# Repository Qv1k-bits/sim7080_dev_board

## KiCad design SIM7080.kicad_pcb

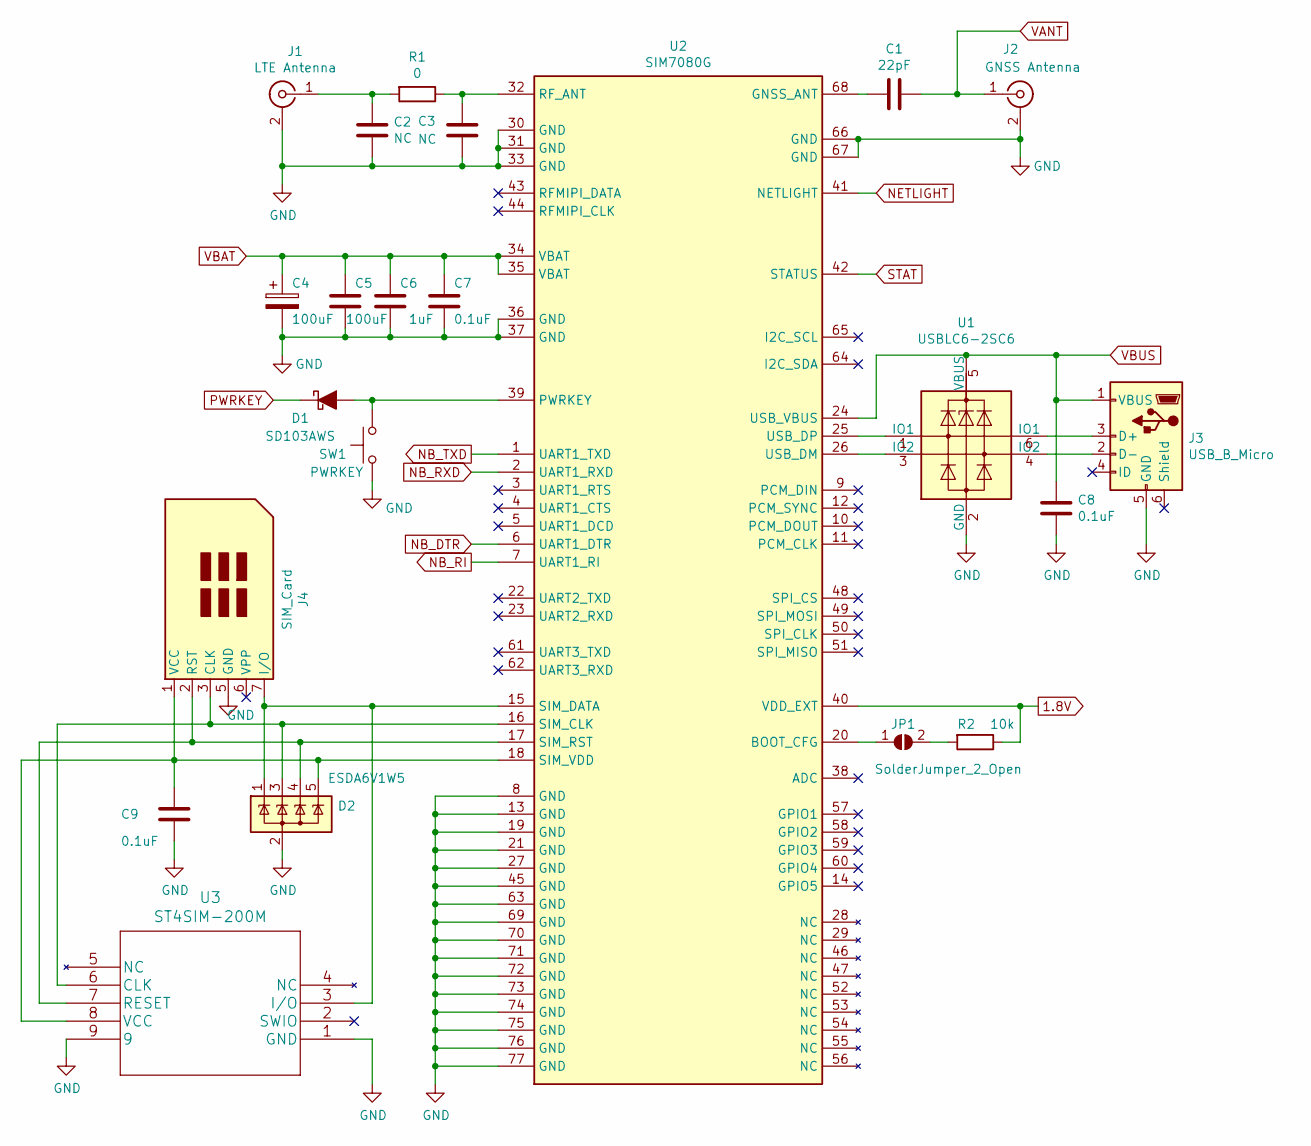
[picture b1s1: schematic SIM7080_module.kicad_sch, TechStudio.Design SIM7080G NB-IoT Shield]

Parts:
C1: 22pF; C_0603_1608Metric_Pad1.05x0.95mm_HandSolder
C2, C3: NC; C_0603_1608Metric_Pad1.05x0.95mm_HandSolder
C4: 100uF; CP_EIA-3528-12_Kemet-T_Pad1.50x2.35mm_HandSolder
C5: 100uF; C_1206_3216Metric_Pad1.42x1.75mm_HandSolder
C6: 1uF; C_0603_1608Metric_Pad1.05x0.95mm_HandSolder
C7, C8, C9: 0.1uF; C_0603_1608Metric_Pad1.05x0.95mm_HandSolder
D1: SD103AWS; D_SOD-323_HandSoldering
D2: ESDA6V1W5; SOT-353_SC-70-5_Handsoldering
J1: LTE Antenna; U.FL_Hirose_U.FL-R-SMT-1_Vertical
J2: GNSS Antenna; U.FL_Hirose_U.FL-R-SMT-1_Vertical
J3: USB_B_Micro; U254-051T-4BH83
J4: SIM_Card; HOAUC-HYC240-SIM-06-150_C645501
JP1: SolderJumper_2_Open; SolderJumper-2_P1.3mm_Open_Pad1.0x1.5mm
R1: 0; R_0603_1608Metric_Pad1.05x0.95mm_HandSolder
R2: 10k; R_0603_1608Metric_Pad1.05x0.95mm_HandSolder
SW1: PWRKEY; SW_TS-1101-X-X
U1: USBLC6-2SC6; SOT-23-6_Handsoldering
U2: SIM7080G
U3: ST4SIM-200M

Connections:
1.8V: R2.1, U2.40 (VDD_EXT); also elsewhere on the board
GND: C2.2, C3.2, C4.2, C5.2, C6.2, C7.2, C8.2, C9.2, D2.2 (A), J1.2 (Ext), J2.2 (Ext), J3.5 (GND), J4.5 (GND), SW1.1, U1.2 (GND), U2.8 (GND), U2.13 (GND), U2.19 (GND), U2.21 (GND), U2.27 (GND), U2.30 (GND), U2.31 (GND), U2.33 (GND), U2.36 (GND), U2.37 (GND), U2.45 (GND), U2.63 (GND), U2.66 (GND), U2.67 (GND), U2.69 (GND), U2.70 (GND), U2.71 (GND), U2.72 (GND), U2.73 (GND), U2.74 (GND), U2.75 (GND), U2.76 (GND), U2.77 (GND), U3.1 (GND), U3.9; also elsewhere on the board
NB_DTR: U2.6 (UART1_DTR); also elsewhere on the board
NB_RI: U2.7 (UART1_RI); also elsewhere on the board
NB_RXD: U2.2 (UART1_RXD); also elsewhere on the board
NB_TXD: U2.1 (UART1_TXD); also elsewhere on the board
NETLIGHT: U2.41 (NETLIGHT); also elsewhere on the board
unnamed: C1.1, U2.68 (GNSS_ANT)
unnamed: C2.1, J1.1 (In), R1.2
unnamed: C3.1, R1.1, U2.32 (RF_ANT)
unnamed: C9.1, D2.5 (K), J4.1 (VCC), U2.18 (SIM_VDD), U3.8 (VCC)
unnamed: D1.2 (A), SW1.2, U2.39 (PWRKEY)
unnamed: D2.1 (K), J4.7 (I/O), U2.15 (SIM_DATA), U3.3 (I/O)
unnamed: D2.3 (K), J4.3 (CLK), U2.16 (SIM_CLK), U3.6 (CLK)
unnamed: D2.4 (K), J4.2 (RST), U2.17 (SIM_RST), U3.7 (RESET)
unnamed: J3.2 (D-), U1.4 (IO2)
unnamed: J3.3 (D+), U1.6 (IO1)
unnamed: JP1.1 (A), U2.20 (BOOT_CFG)
unnamed: JP1.2 (B), R2.2
unnamed: U1.1 (IO1), U2.25 (USB_DP)
unnamed: U1.3 (IO2), U2.26 (USB_DM)
PWRKEY: D1.1 (K); also elsewhere on the board
STAT: U2.42 (STATUS); also elsewhere on the board
VANT: C1.2, J2.1 (In); also elsewhere on the board
VBAT: C4.1, C5.1, C6.1, C7.1, U2.34 (VBAT), U2.35 (VBAT); also elsewhere on the board
VBUS: C8.1, J3.1 (VBUS), U1.5 (VBUS), U2.24 (USB_VBUS); also elsewhere on the board

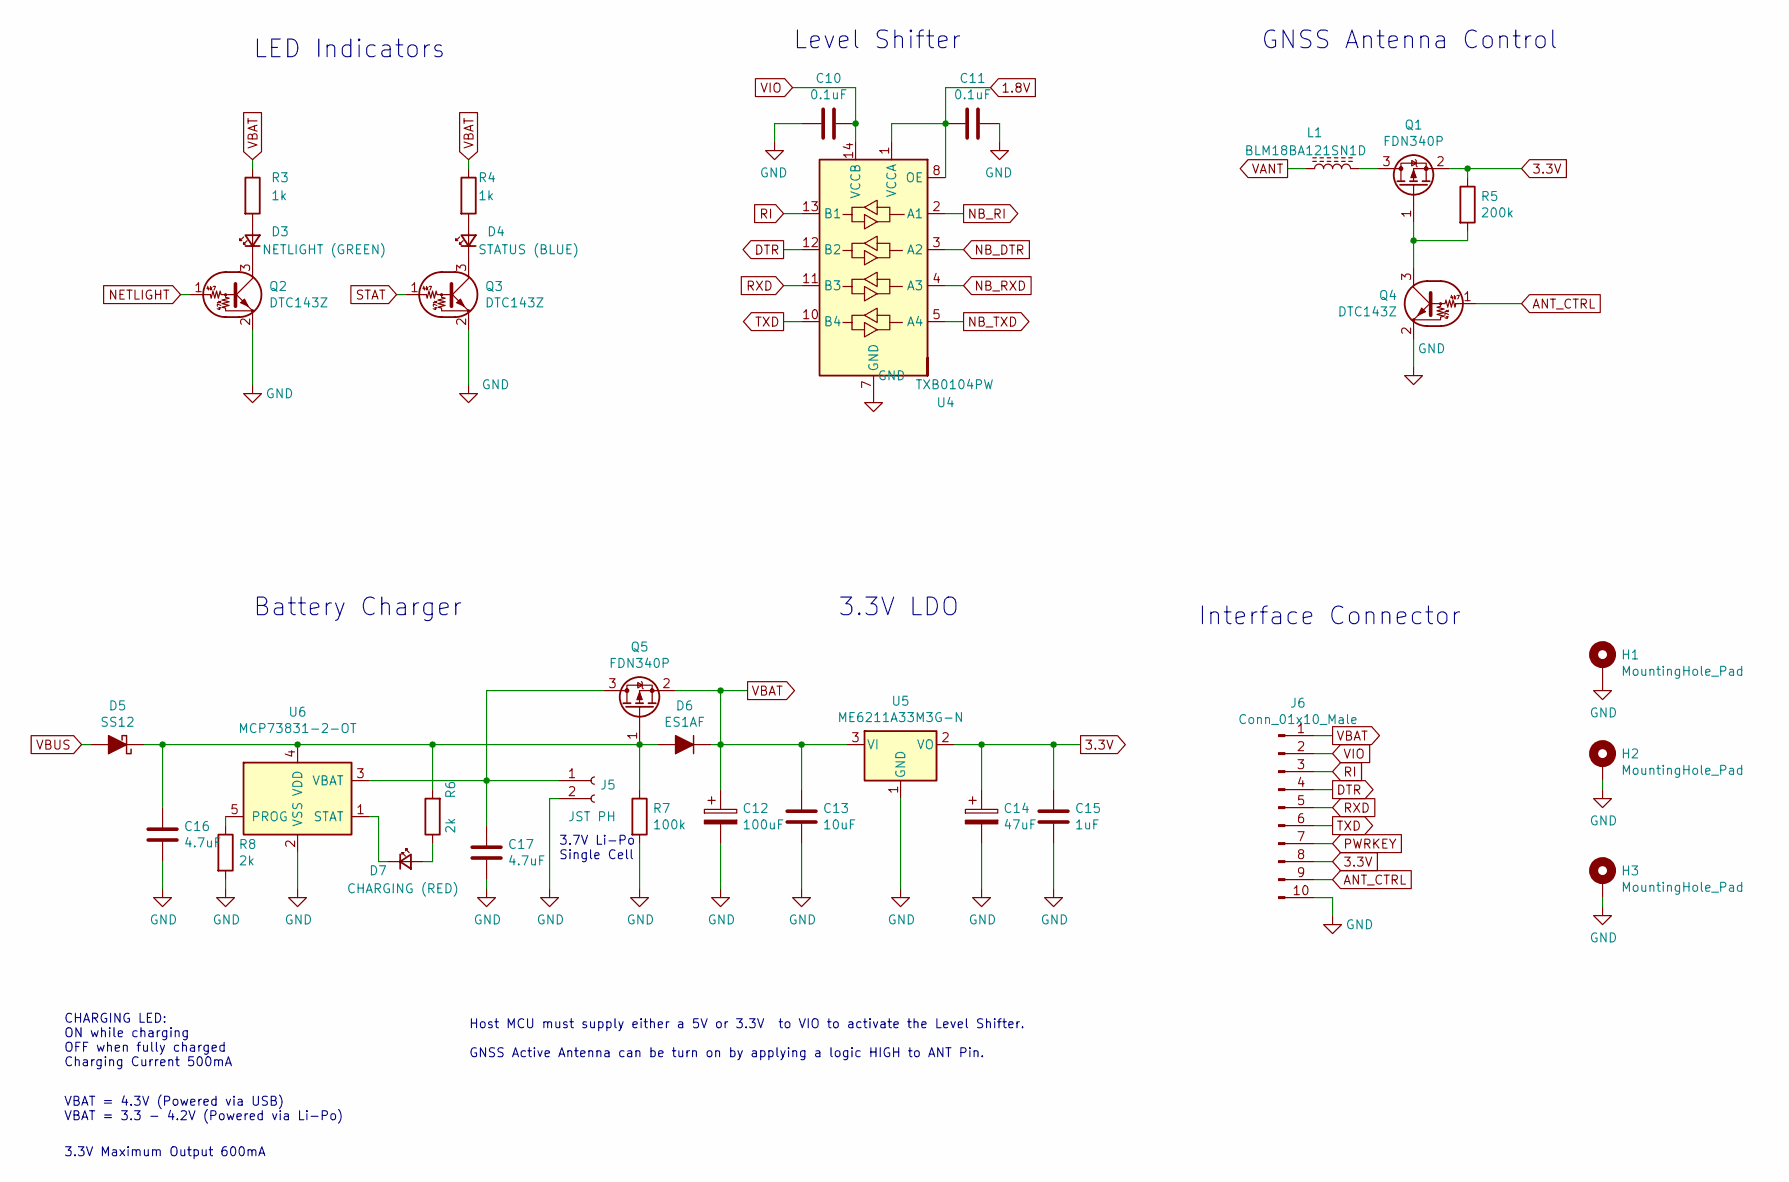
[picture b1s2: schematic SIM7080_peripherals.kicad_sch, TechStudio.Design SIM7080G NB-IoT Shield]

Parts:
C10, C11: 0.1uF; C_0603_1608Metric_Pad1.05x0.95mm_HandSolder
C12: 100uF; CP_EIA-3528-12_Kemet-T_Pad1.50x2.35mm_HandSolder
C13: 10uF; C_0603_1608Metric_Pad1.05x0.95mm_HandSolder
C14: 47uF; CP_EIA-3216-10_Kemet-I_Pad1.58x1.35mm_HandSolder
C15: 1uF; C_0603_1608Metric_Pad1.05x0.95mm_HandSolder
C16, C17: 4.7uF; C_0603_1608Metric_Pad1.05x0.95mm_HandSolder
D3: NETLIGHT (GREEN); LED_0603_1608Metric_Pad1.05x0.95mm_HandSolder
D4: STATUS (BLUE); LED_0603_1608Metric_Pad1.05x0.95mm_HandSolder
D5: SS12; D_SMA
D6: ES1AF; D_SMA
D7: CHARGING (RED); LED_0603_1608Metric_Pad1.05x0.95mm_HandSolder
H1, H2, H3: MountingHole_Pad; MountingHole_2.7mm_M2.5
J5: JST PH; JST_PH_S2B-PH-K_1x02_P2.00mm_Horizontal
J6: Conn_01x10_Male; PinHeader_1x10_P2.54mm_Horizontal
L1: BLM18BA121SN1D; L_0603_1608Metric_Pad1.05x0.95mm_HandSolder
Q1, Q5: FDN340P; SOT-23_Handsoldering
Q2, Q3, Q4: DTC143Z; SOT523
R3, R4: 1k; R_0603_1608Metric_Pad1.05x0.95mm_HandSolder
R5: 200k; R_0603_1608Metric_Pad1.05x0.95mm_HandSolder
R6, R8: 2k; R_0603_1608Metric_Pad1.05x0.95mm_HandSolder
R7: 100k; R_0603_1608Metric_Pad1.05x0.95mm_HandSolder
U4: TXB0104PW; TSSOP-14_4.4x5mm_P0.65mm
U5: ME6211A33M3G-N; SOT-23
U6: MCP73831-2-OT; SOT-23-5_HandSoldering

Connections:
1.8V: C11.2, U4.1 (VCCA), U4.8 (OE); also elsewhere on the board
3.3V: C14.1, C15.1, J6.8, Q1.2 (S), R5.1, U5.2 (VO)
ANT_CTRL: J6.9, Q4.1 (B)
DTR: J6.4, U4.12 (B2)
GND: C10.2, C11.1, C12.2, C13.2, C14.2, C15.2, C16.2, C17.2, H1.1, H2.1, H3.1, J5.2, J6.10, Q2.2 (E), Q3.2 (E), Q4.2 (E), R7.2, R8.2, U4.7 (GND), U5.1 (GND), U6.2 (VSS); also elsewhere on the board
NB_DTR: U4.3 (A2); also elsewhere on the board
NB_RI: U4.2 (A1); also elsewhere on the board
NB_RXD: U4.4 (A3); also elsewhere on the board
NB_TXD: U4.5 (A4); also elsewhere on the board
NETLIGHT: Q2.1 (B); also elsewhere on the board
unnamed: C16.1, D5.1 (K), D6.2 (A), Q5.1 (G), R6.2, R7.1, U6.4 (VDD)
unnamed: C17.1, J5.1, Q5.3 (D), U6.3 (VBAT)
unnamed: D3.1 (K), Q2.3 (C)
unnamed: D3.2 (A), R3.2
unnamed: D4.1 (K), Q3.3 (C)
unnamed: D4.2 (A), R4.2
unnamed: D7.1 (K), U6.1 (STAT)
unnamed: D7.2 (A), R6.1
unnamed: L1.2, Q1.3 (D)
unnamed: Q1.1 (G), Q4.3 (C), R5.2
unnamed: R8.1, U6.5 (PROG)
PWRKEY: J6.7; also elsewhere on the board
RI: J6.3, U4.13 (B1)
RXD: J6.5, U4.11 (B3)
STAT: Q3.1 (B); also elsewhere on the board
TXD: J6.6, U4.10 (B4)
VANT: L1.1; also elsewhere on the board
VBAT: C12.1, C13.1, D6.1 (K), J6.1, Q5.2 (S), R3.1, R4.1, U5.3 (VI); also elsewhere on the board
VBUS: D5.2 (A); also elsewhere on the board
VIO: C10.1, J6.2, U4.14 (VCCB)

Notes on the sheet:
LED Indicators
Interface Connector
3.7V Li-Po Single Cell
Battery Charger
Host MCU must supply either a 5V or 3.3V to VIO to activate the Level Shifter. GNSS Active Antenna can be turn on by applying a logic HIGH to ANT Pin.
Level Shifter
VBAT = 4.3V (Powered via USB) VBAT = 3.3 - 4.2V (Powered via Li-Po)
3.3V LDO
CHARGING LED: ON while charging OFF when fully charged Charging Current 500mA
GNSS Antenna Control
3.3V Maximum Output 600mA

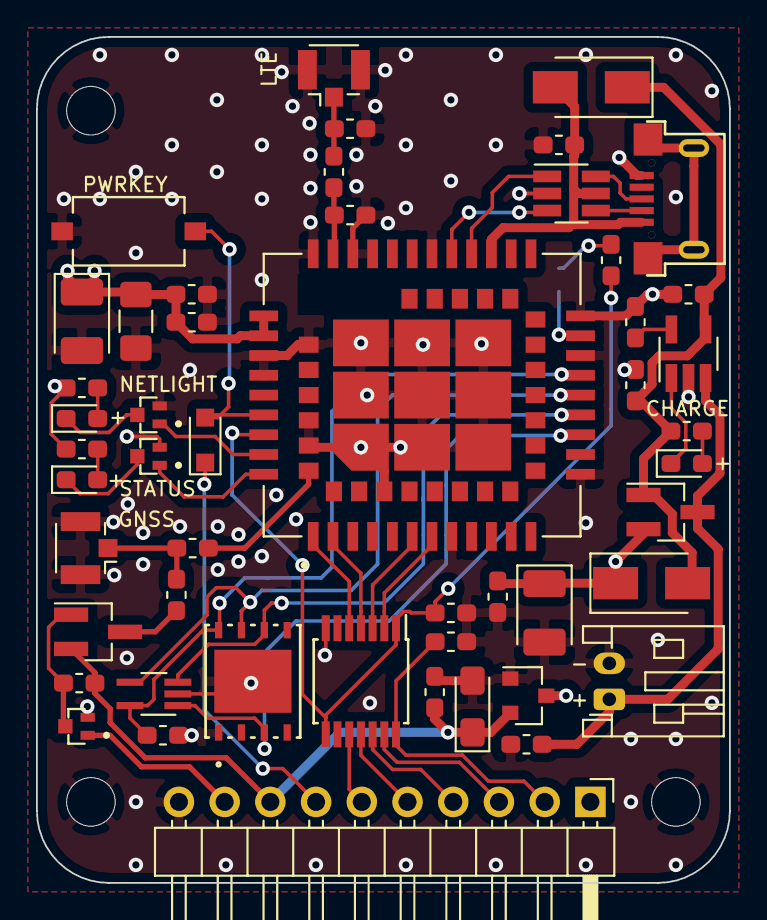
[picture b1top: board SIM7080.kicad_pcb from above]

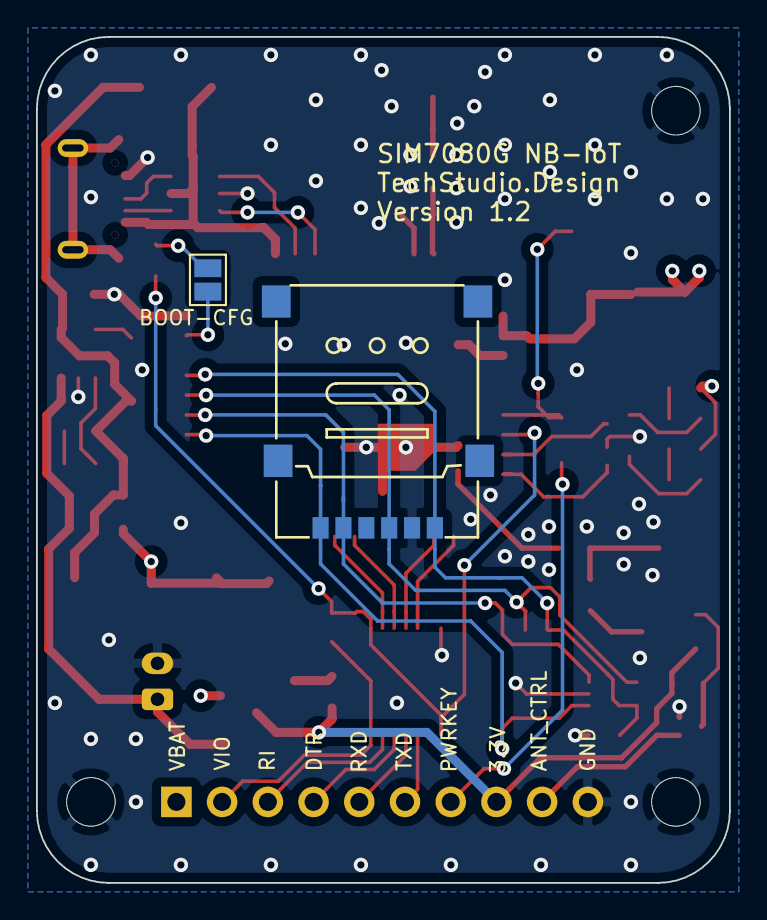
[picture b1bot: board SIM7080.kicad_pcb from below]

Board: 4 copper layers, 38.5 x 47.0 mm, 55 parts (2 on the bottom side), 44 nets.

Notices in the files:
SIM7080.kicad_pcb:
Copyright: Tech Studio Design, 2021
